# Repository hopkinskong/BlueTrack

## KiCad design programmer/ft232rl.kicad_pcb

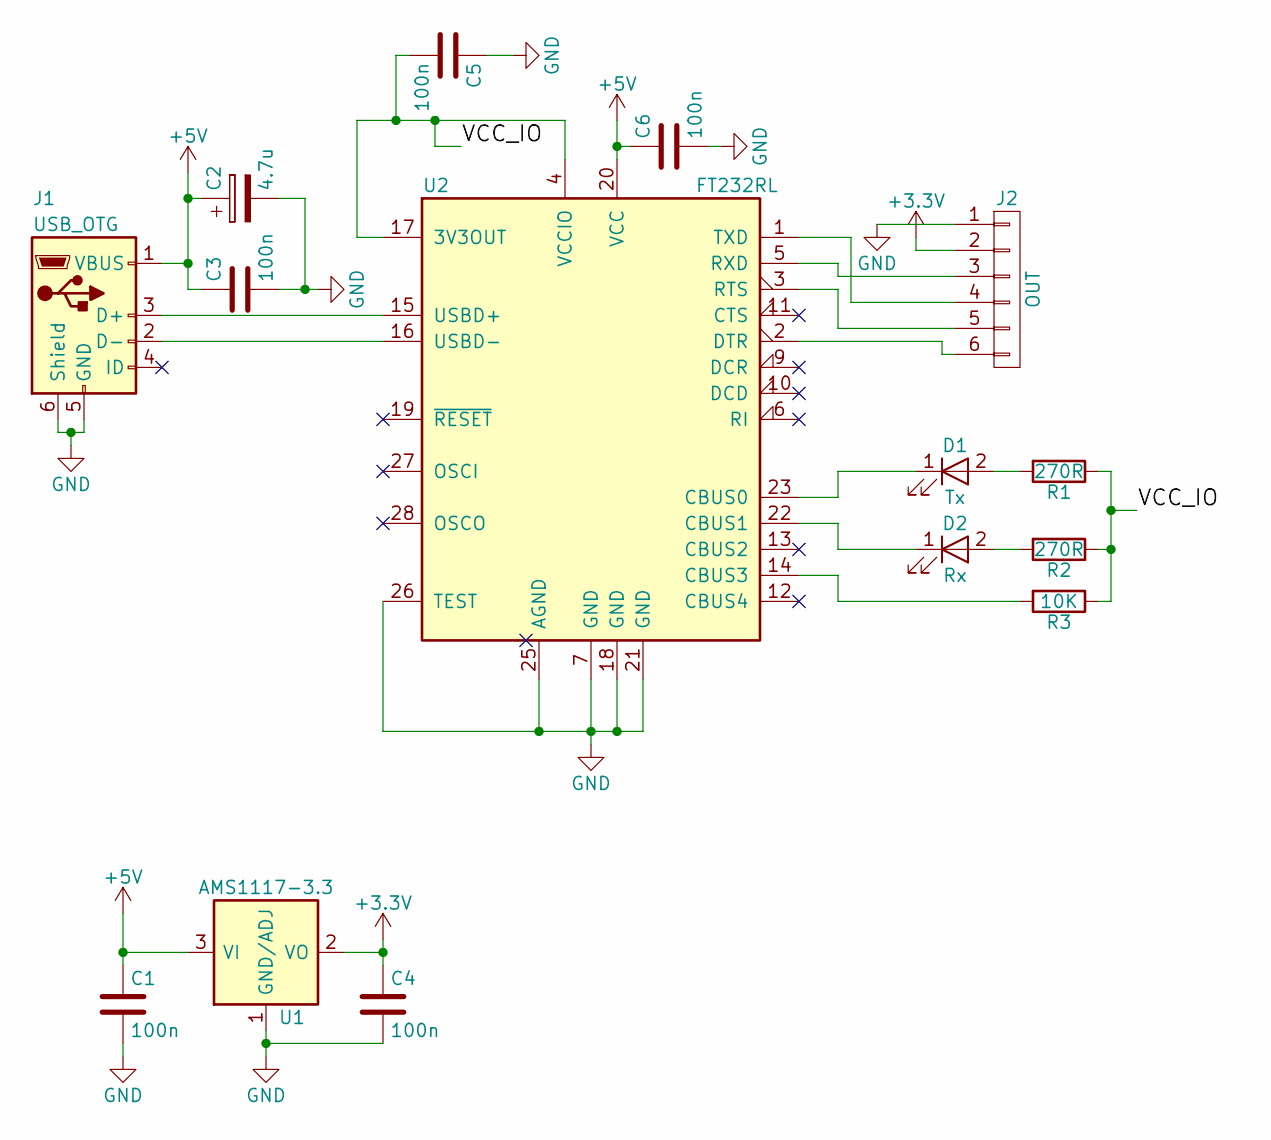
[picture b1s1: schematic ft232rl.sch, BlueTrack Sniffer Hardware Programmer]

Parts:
C1, C3, C4, C5, C6: 100n; C_0805_HandSoldering
C2: 4.7u; C_1206_HandSoldering
D1: Tx; LED_1206_HandSoldering
D2: Rx; LED_1206_HandSoldering
J1: USB_OTG; USB_Micro-B_Molex_47346-0001
J2: OUT; Molex_KK-6410-06_06x2.54mm_Straight
R1, R2: 270R; R_0805_HandSoldering
R3: 10K; R_1206_HandSoldering
U1: AMS1117-3.3; SOT-223
U2: FT232RL; SSOP-28_5.3x10.2mm_Pitch0.65mm

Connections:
+3V3: C4.1, J2.2, U1.2 (VO), U1.4 (VO)
+5V: C1.1, C2.1, C3.1, C6.1, J1.1 (VBUS), U1.3 (VI), U2.20 (VCC)
/VCC_IO: C5.2, R1.1, R2.1, R3.1, U2.4 (VCCIO), U2.17 (3V3OUT)
GND: C1.2, C2.2, C3.2, C4.2, C5.1, C6.2, J1.5 (GND), J1.6 (Shield), J2.1, U1.1 (GND/ADJ), U2.7 (GND), U2.18 (GND), U2.21 (GND), U2.25 (AGND), U2.26 (TEST)
unnamed: D1.1 (K), U2.23 (CBUS0)
unnamed: D1.2 (A), R1.2
unnamed: D2.1 (K), U2.22 (CBUS1)
unnamed: D2.2 (A), R2.2
unnamed: J1.2 (D-), U2.16 (USBD-)
unnamed: J1.3 (D+), U2.15 (USBD+)
unnamed: J2.3, U2.5 (RXD)
unnamed: J2.4, U2.1 (TXD)
unnamed: J2.5, U2.3 (RTS)
unnamed: J2.6, U2.2 (DTR)
unnamed: R3.2, U2.14 (CBUS3)

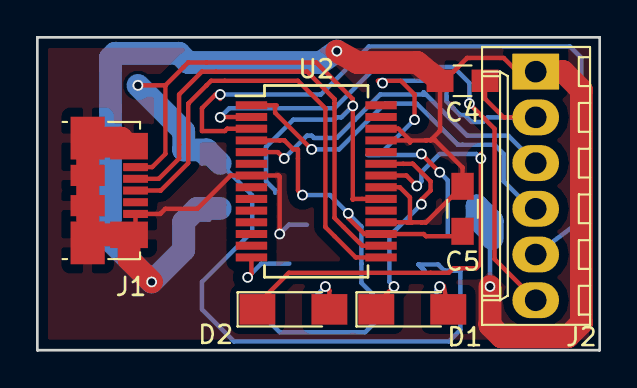
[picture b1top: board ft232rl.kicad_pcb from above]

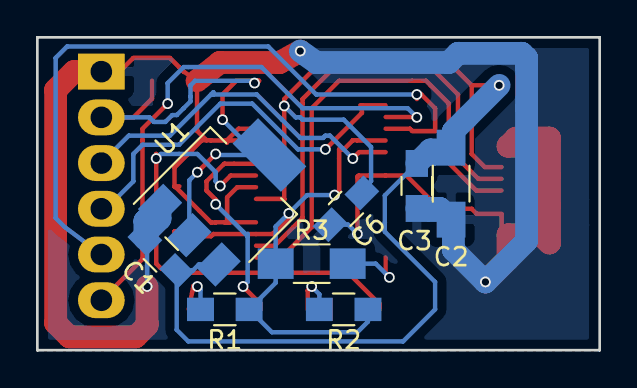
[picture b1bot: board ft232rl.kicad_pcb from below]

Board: 2 copper layers, 31.2 x 17.4 mm, 15 parts (8 on the bottom side), 15 nets.

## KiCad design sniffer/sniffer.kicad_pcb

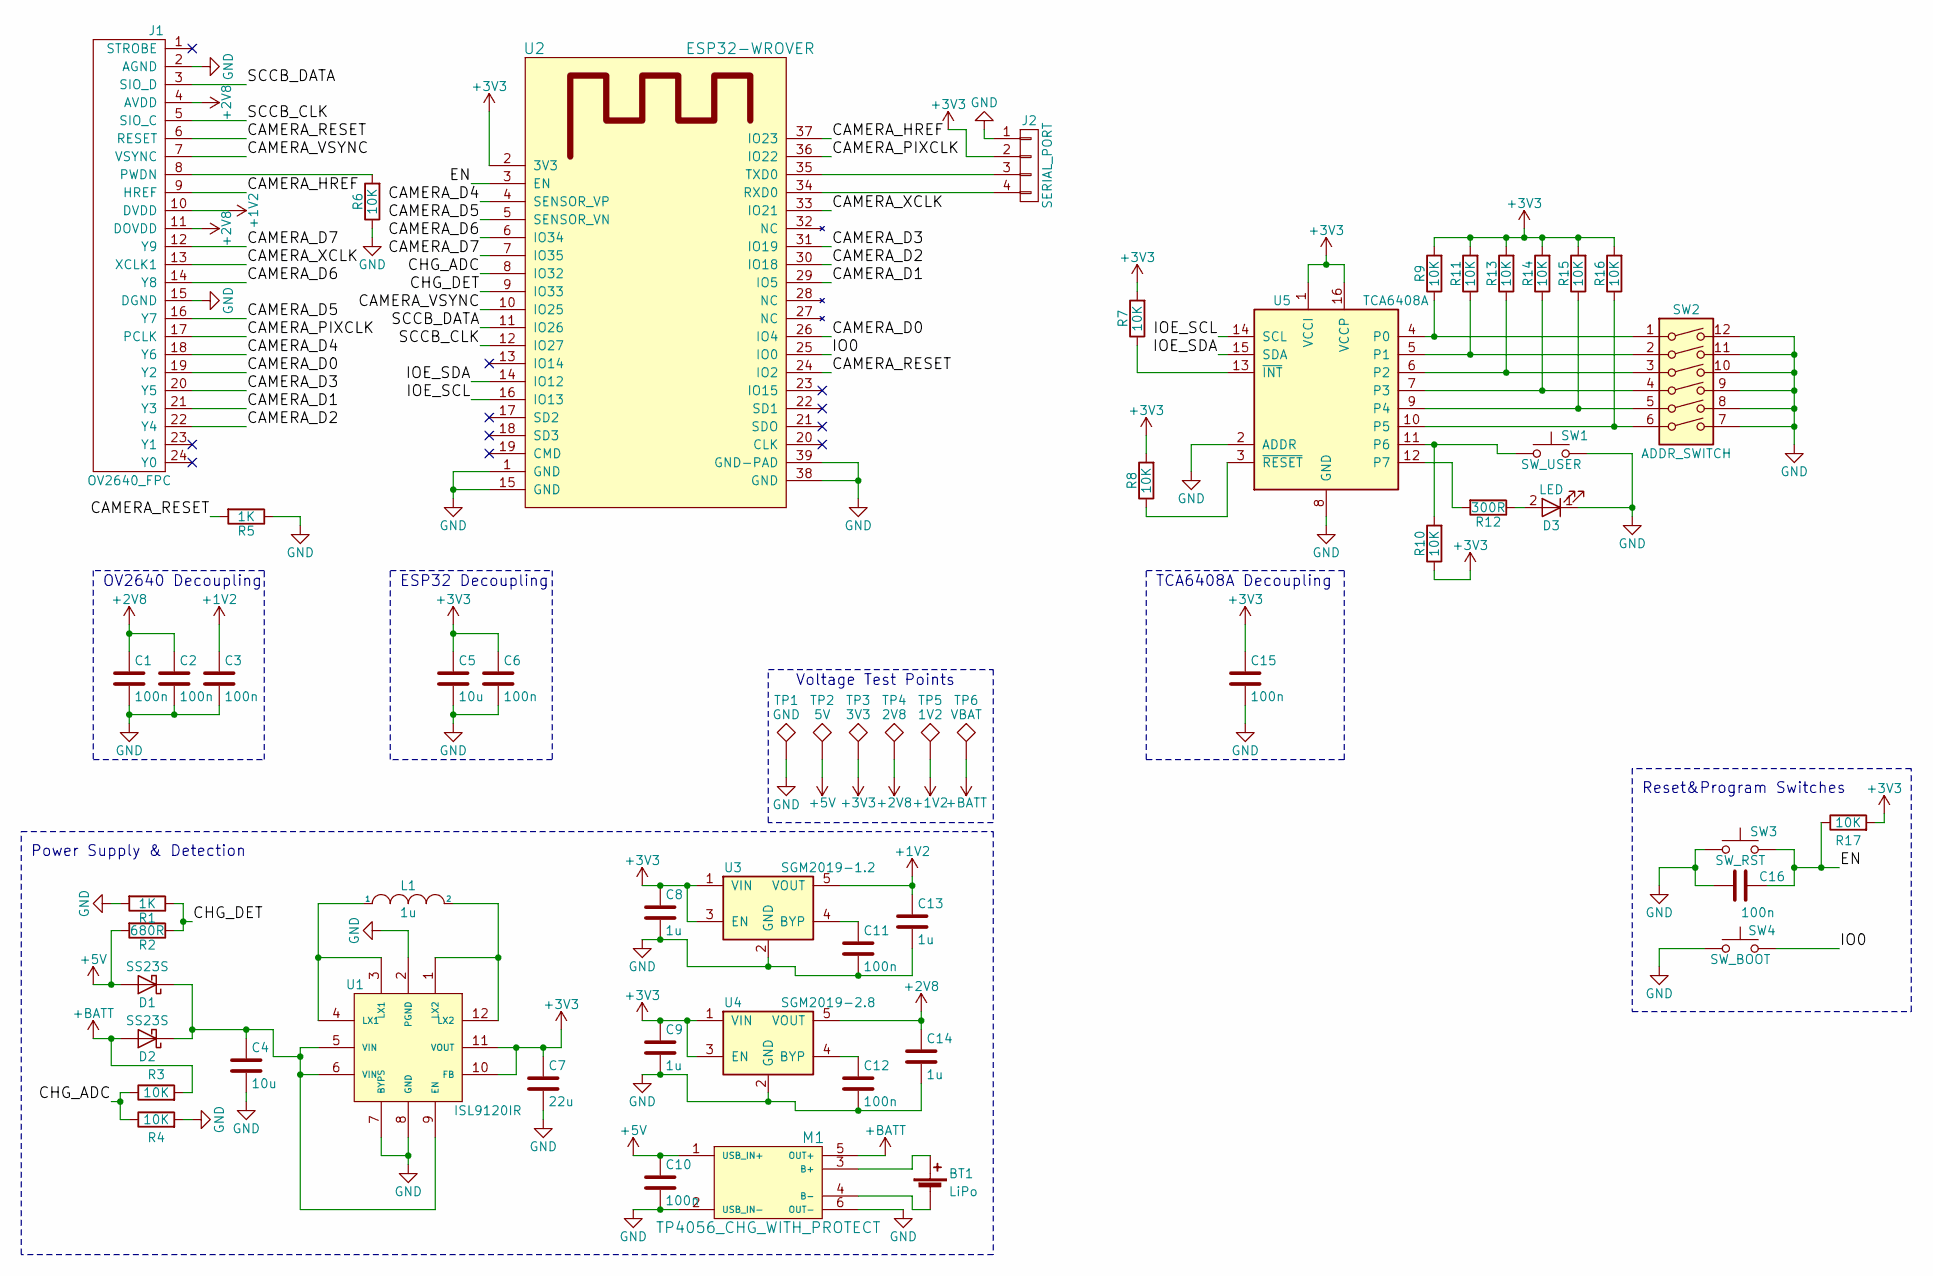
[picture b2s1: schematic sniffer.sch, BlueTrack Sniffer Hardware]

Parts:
BT1: LiPo; Molex_KK-6410-02_02x2.54mm_Straight
C1, C2, C3, C6, C10, C11, C12, C15, C16: 100n; C_0805_HandSoldering
C4, C5: 10u; C_0805_HandSoldering
C7: 22u; C_1206_HandSoldering
C8, C9, C13, C14: 1u; C_1206_HandSoldering
D1, D2: SS23S; D_SMA
D3: LED; LED_1206_HandSoldering
J1: OV2640_FPC; OV2640_FPC_24
J2: SERIAL_PORT; Pin_Header_Straight_1x04_Pitch2.54mm
L1: 1u; Inductor_LQH3NP
M1: TP4056_CHG_WITH_PROTECT; 4056_fixed
R1, R5: 1K; R_0805_HandSoldering
R2: 680R; R_0805_HandSoldering
R3, R4, R6, R7, R8, R9, R10, R11, R13, R14, R15, R16, R17: 10K; R_1206_HandSoldering
R12: 300R; R_0805_HandSoldering
SW1: SW_USER; SW_PUSH_6mm
SW2: ADDR_SWITCH; SW_DIP_x6_W8.61mm_Slide_LowProfile
SW3: SW_RST; SW_PUSH_6mm
SW4: SW_BOOT; SW_PUSH_6mm
TP1: GND; TP
TP2: 5V; TP
TP3: 3V3; TP
TP4: 2V8; TP
TP5: 1V2; TP
TP6: VBAT; TP
U1: ISL9120IR; QFN-12-1EP_3x3mm_Pitch0.5mm
U2: ESP32-WROVER
U3: SGM2019-1.2; SOT-23-5
U4: SGM2019-2.8; SOT-23-5
U5: TCA6408A; TSSOP-16_4.4x5mm_Pitch0.65mm

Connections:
+1V2: C3.1, C13.1, J1.10 (DVDD), TP5.1, U3.5 (VOUT)
+2V8: C1.1, C2.1, C14.1, J1.4 (AVDD), J1.11 (DOVDD), TP4.1, U4.5 (VOUT)
+3V3: C5.1, C6.1, C7.1, C8.1, C9.1, C15.1, J2.2, R7.2, R8.2, R9.2, R10.1, R11.2, R13.2, R14.2, R15.2, R16.2, R17.2, TP3.1, U1.10 (FB), U1.11 (VOUT), U2.2 (3V3), U3.1 (VIN), U3.3 (EN), U4.1 (VIN), U4.3 (EN), U5.1 (VCCI), U5.16 (VCCP)
+5V: C10.1, D1.2 (A), M1.1 (USB_IN+), R2.2, TP2.1
+BATT: D2.2 (A), M1.5 (OUT+), R3.2, TP6.1
/CAMERA_D0: J1.19 (Y2), U2.26 (IO4)
/CAMERA_D1: J1.21 (Y3), U2.29 (IO5)
/CAMERA_D2: J1.22 (Y4), U2.30 (IO18)
/CAMERA_D3: J1.20 (Y5), U2.31 (IO19)
/CAMERA_D4: J1.18 (Y6), U2.4 (SENSOR_VP)
/CAMERA_D5: J1.16 (Y7), U2.5 (SENSOR_VN)
/CAMERA_D6: J1.14 (Y8), U2.6 (IO34)
/CAMERA_D7: J1.12 (Y9), U2.7 (IO35)
/CAMERA_HREF: J1.9 (HREF), U2.37 (IO23)
/CAMERA_PIXCLK: J1.17 (PCLK), U2.36 (IO22)
/CAMERA_RESET: J1.6 (RESET), R5.2, U2.24 (IO2)
/CAMERA_VSYNC: J1.7 (VSYNC), U2.10 (IO25)
/CAMERA_XCLK: J1.13 (XCLK1), U2.33 (IO21)
/CHG_ADC: R3.1, R4.1, U2.8 (IO32)
/CHG_DET: R1.1, R2.1, U2.9 (IO33)
/EN: C16.1, R17.1, SW3.2, U2.3 (EN)
/IO0: SW4.1, U2.25 (IO0)
/IOE_SCL: U2.16 (IO13), U5.14 (SCL)
/IOE_SDA: U2.14 (IO12), U5.15 (SDA)
/SCCB_CLK: J1.5 (SIO_C), U2.12 (IO27)
/SCCB_DATA: J1.3 (SIO_D), U2.11 (IO26)
GND: C1.2, C2.2, C3.2, C4.2, C5.2, C6.2, C7.2, C8.2, C9.2, C10.2, C11.2, C12.2, C13.2, C14.2, C15.2, C16.2, D3.1 (K), J1.2 (AGND), J1.15 (DGND), J2.1, M1.2 (USB_IN-), M1.6 (OUT-), R1.2, R4.2, R5.1, R6.1, SW1.2, SW2.7, SW2.8, SW2.9, SW2.10, SW2.11, SW2.12, SW3.1, SW4.2, TP1.1, U1.2 (PGND), U1.7 (BYPS), U1.8 (GND), U2.1 (GND), U2.15 (GND), U2.38 (GND), U2.39 (GND-PAD), U3.2 (GND), U4.2 (GND), U5.2 (ADDR), U5.8 (GND)
unnamed: BT1.1 (+), M1.3 (B+)
unnamed: BT1.2 (-), M1.4 (B-)
unnamed: C4.1, D1.1 (K), D2.1 (K), U1.5 (VIN), U1.6 (VIN), U1.9 (EN)
unnamed: C11.1, U3.4 (BYP)
unnamed: C12.1, U4.4 (BYP)
unnamed: D3.2 (A), R12.1
unnamed: J1.8 (PWDN), R6.2
unnamed: J2.3, U2.35 (TXD0)
unnamed: J2.4, U2.34 (RXD0)
unnamed: L1.1, U1.3 (LX1), U1.4 (LX1)
unnamed: L1.2, U1.1 (LX2), U1.12 (LX2)
unnamed: R7.1, U5.13 (~INT~)
unnamed: R8.1, U5.3 (~RESET)
unnamed: R9.1, SW2.1, U5.4 (P0)
unnamed: R10.2, SW1.1, U5.11 (P6)
unnamed: R11.1, SW2.2, U5.5 (P1)
unnamed: R12.2, U5.12 (P7)
unnamed: R13.1, SW2.3, U5.6 (P2)
unnamed: R14.1, SW2.4, U5.7 (P3)
unnamed: R15.1, SW2.5, U5.9 (P4)
unnamed: R16.1, SW2.6, U5.10 (P5)

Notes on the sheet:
Power Supply & Detection
Reset&Program Switches
OV2640 Decoupling
ESP32 Decoupling
TCA6408A Decoupling
Voltage Test Points

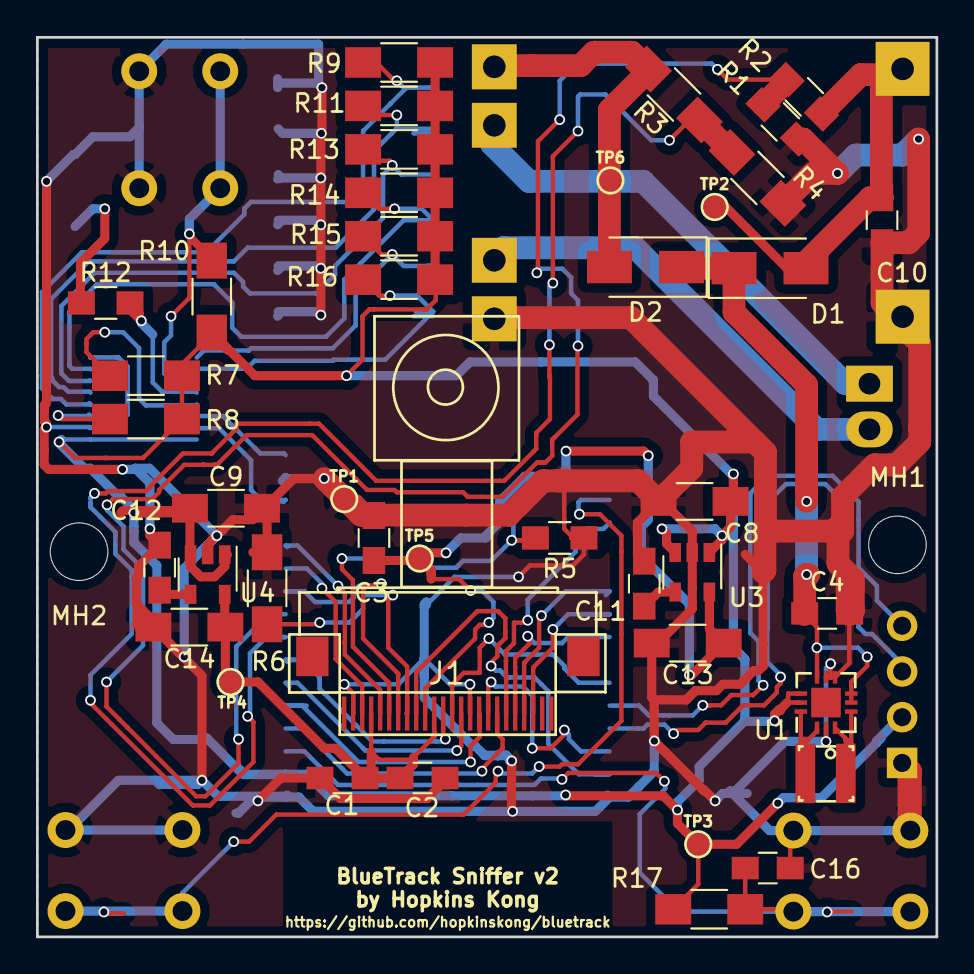
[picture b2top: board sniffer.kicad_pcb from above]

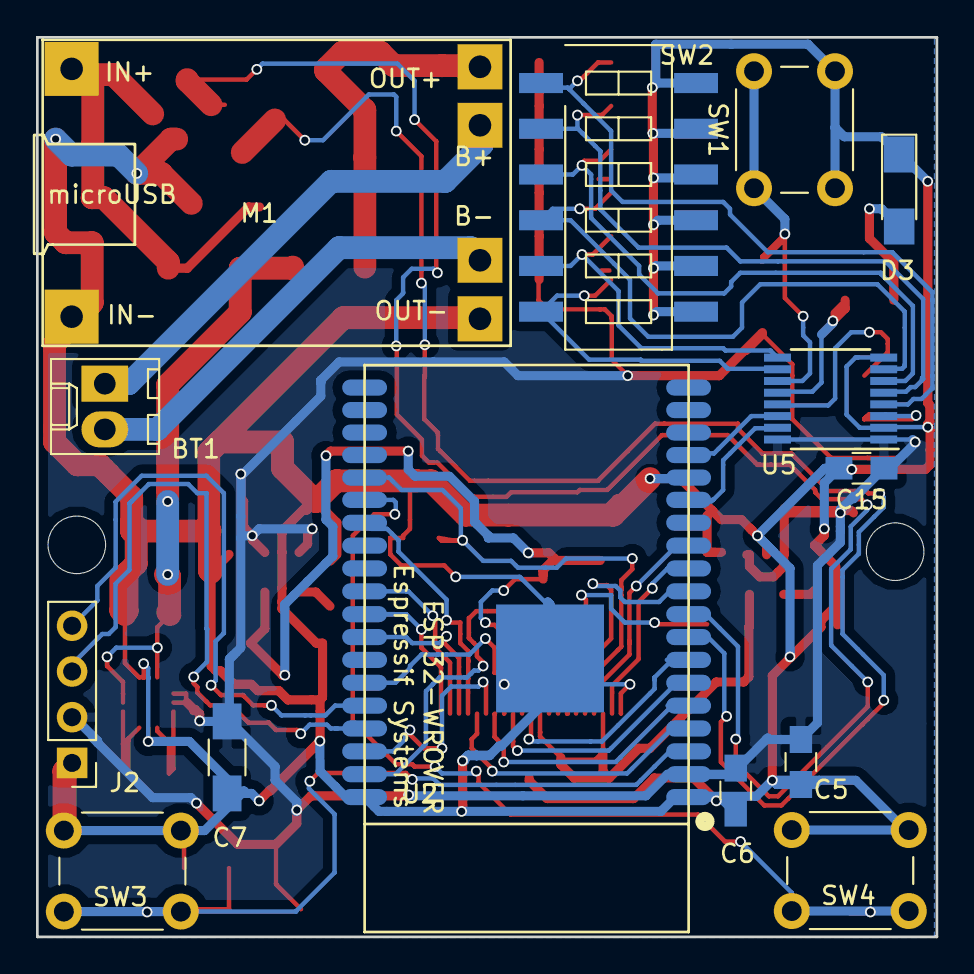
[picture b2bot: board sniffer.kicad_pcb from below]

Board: 2 copper layers, 50.0 x 50.0 mm, 58 parts (14 on the bottom side), 48 nets.

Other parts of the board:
MH1, MH2: MountingHole_3.2mm_M3_ISO14580

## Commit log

2017-05-17 Add submodule bluetrack-webapp points to branch with same name
2017-05-17 Add submodule bluetrack-hardware points to branch with same name
2017-05-17 Re-add .gitmodules
2017-05-21 Application basic structure is done.
2017-05-21 Updated submodule to newer version.
2018-04-24 Hardware Done
2018-04-24 Prepare to switch to node.js
2018-04-24 Remove htaccess
2018-04-24 Node.js is used as webapp now.
2018-04-24 Add submodules
2018-04-24 Adding submodules folders
